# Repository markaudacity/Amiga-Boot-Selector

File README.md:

# Amiga Boot Selector

This is a Floppy Switcher for the Amiga 500/2000. It allows you to
switch DF0/DF1, making it possible to boot from either a Gotek drive
or the internal floppy drive. without relying on AmigaOS.

## About

This work is a derivative of the [Amiga Boot Selector by
Jussi Kilpeläinen](https://jussikilpelainen.kapsi.fi/wordpress/?p=256)

This redesign puts the pin header for the switch to the side, reducing
the footprint of the adapter. The project was mainly born out of the fact
that I could not buy a ready-made version of a boot selector in the US
(several European sellers bailed out on me)

Since I had to order my own PCBs anyway, I decided to optimize the design
a bit for my use case.

## Bill of Materials

Here's the [Bill of Materials (BOM)](https://htmlpreview.github.io/?https://raw.githubusercontent.com/reinauer/Amiga-Boot-Selector/main/bom.html).

## Make your own

* [PCBWay](https://www.pcbway.com/project/shareproject/Amiga_Boot_Selector_1.html)
* [OSHpark](https://oshpark.com/shared_projects/dJHz8dkw)

## Credits

Big thank you goes to Jussi Kilpeläinen for the original design

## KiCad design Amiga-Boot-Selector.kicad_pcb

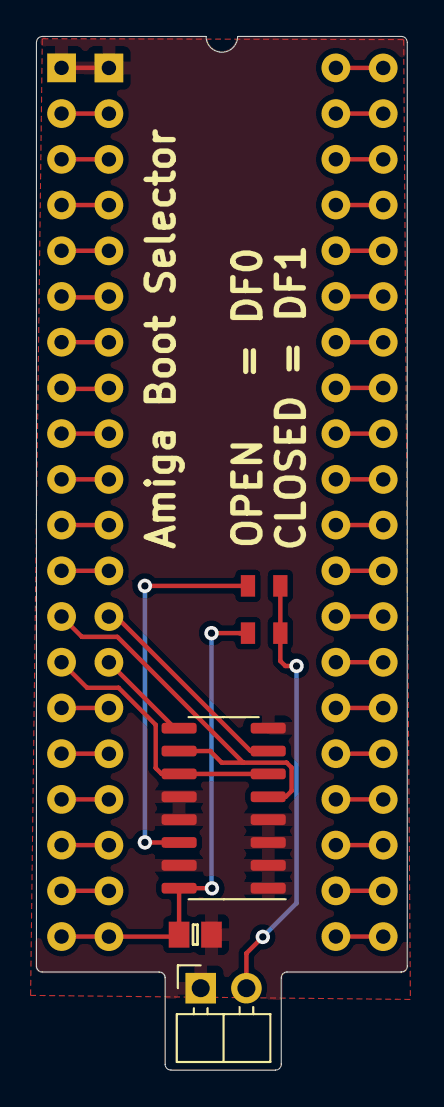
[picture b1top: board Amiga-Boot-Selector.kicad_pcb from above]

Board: 2 copper layers, 20.6 x 57.4 mm, 7 parts (1 on the bottom side), 44 nets.

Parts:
C1: 0.1UF; 0805
J1: Conn_01x02; PinHeader_1x02_P2.54mm_Horizontal
R1: 10K; 0805
R2: 330R; 0805
U1: CIA8520 socket; DIP-40_W15.24mm
U2: 74LS153; SOIC-16_3.9x9.9mm_P1.27mm
U3: CIA8520 pin header; DIP-40_W15.24mm

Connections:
/13A: U1.13, U2.5, U2.10
/13B: U2.7, U3.13
/14A: U1.14, U2.6, U2.11
/14B: U2.9, U3.14
/_cs: U1.23, U3.23
/_f: U1.24, U3.24
/_int: U1.21, U3.21
/_pc: U1.18, U3.18
/_reset: U1.34, U3.34
/_w: U1.22, U3.22
/c: U1.40, U3.40
/d0: U1.33, U3.33
/d1: U1.32, U3.32
/d2: U1.31, U3.31
/d3: U1.30, U3.30
/d4: U1.29, U3.29
/d5: U1.28, U3.28
/d6: U1.27, U3.27
/d7: U1.26, U3.26
/e: U1.25, U3.25
/pa0: U1.2, U3.2
/pa1: U1.3, U3.3
/pa2: U1.4, U3.4
/pa3: U1.5, U3.5
/pa4: U1.6, U3.6
/pa5: U1.7, U3.7
/pa6: U1.8, U3.8
/pa7: U1.9, U3.9
/pb0: U1.10, U3.10
/pb1: U1.11, U3.11
/pb2: U1.12, U3.12
/pb5: U1.15, U3.15
/pb6: U1.16, U3.16
/pb7: U1.17, U3.17
/rs0: U1.38, U3.38
/rs1: U1.37, U3.37
/rs2: U1.36, U3.36
/rs3: U1.35, U3.35
/s: U1.39, U3.39
/tick: U1.19, U3.19
GND: C1.2, J1.1, U1.1, U2.1, U2.2, U2.3, U2.4, U2.8, U2.12, U2.13, U2.15, U3.1
unnamed: J1.2, R1.2, R2.2
unnamed: R2.1, U2.14
VCC: C1.1, R1.1, U1.20, U2.16, U3.20

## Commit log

2026-06-09 added gerber files
2026-06-09 removed gerber folder
    most people only need the gerbers as a ZIP file for uploading
2026-06-09 saved
2026-06-09 rearrange
2026-06-09 testing ssh KiCad

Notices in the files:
Amiga-Boot-Selector.kicad_pcb:
Copyright 2021 Stefan Reinauer
